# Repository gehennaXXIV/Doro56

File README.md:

# Doro56
***

A 56-key split keyboard with a reversible PCB that uses normal mods, an exploded number row, a semi-columnar staggered layout, plus support for rotary encoders. Mainly inspired by Alice layouts and split boards like the Lily58 and Corne.

[ZMK config](https://github.com/gehennaXXIV/zmk-config-Doro56)
 - support for https://nickcoutsos.github.io/keymap-editor/ and https://zmk.studio/

QMK config - None yet - RP2040 Pro Micro support soon

***
## Changelog

#### v1.2 - Minor Edit
- **JST PH Footprint**: The footprint has been updated to avoid the need for manually changing plug polarity. Ensure the Red (+) wire matches the plug's positive pin as the 2 outer pins are negative/ground pins. If your plug isn't matching the indicators, just shift the socket one pin sideways. Note: This socket is installed on the bottom of the half you're building.

#### v1.1 - Minor Edit
- **Caps and Enter Footprints**: Changed to a single reversible footprint (previously used two single key footprints rotated).
- **JST PH Footprint**: Adjusted and relocated for increased flexibility.
- **Plate**: Slightly increased the cutout size for the rotary encoder.
- **PCB Cutout**: Modified to [remove blank space](https://github.com/gehennaXXIV/Doro56/blob/main/pics/v1.1.png) between Control and Alt keys, allowing space for a 402030 battery without increasing the case height clearance.

***
## Build Guide
Quick overview:
* [Solder the MCU](https://raw.githubusercontent.com/gehennaXXIV/Doro56/main/pics/mcu.jpg) with the components facing down, and the TRRS jack on top of the half you are building. For MCU socketing, the footprint was modified to allow [sockets with thick pins to work](https://down-ph.img.susercontent.com/file/sg-11134201-7qvco-ley7fi4ef44v33). You can use milmax pins, or, what I use, harvested gold pins from a 5-pin RGB header (also cheaper). [Sample 2](https://raw.githubusercontent.com/gehennaXXIV/Doro56/main/pics/sockets.jpg)
* Bridge the [jumpers](https://raw.githubusercontent.com/gehennaXXIV/Doro56/main/pics/bridge.jpg) on the MCU from underneath, and add other components such as diodes, MX sockets, and the power switch.

***
## PARTS
| **COMPONENTS**             |  Qty  |  Remarks |
| :------------------------- | :---: | :------  |
| Diodes 1N4148W (SMD)        |  58   | SOD-123  |
| MX Switch Sockets           |  56   |          |
| 2U PCB-Mount Stabilizers    |  04   |          |
| Power Switch                |  02   | MSK12C02 |
| Reset Switch                |  02   | MJTP1250 |
| JST 2 PH Right Angle Jack   |  02   |          |
| TRRS Jack                   |  02   |  MJ-4PP-9 or PJ320A |
| Rotary Encoder              |  02   | EC11 - acrylic case has enough clearance for 22mm knobs |

***
| **MCU**                        |  Qty  |  Remarks |
| :----------------------------- | :---: | :------  |
| Low Profile MCU sockets        |  04   |  The MCU socket footprint was modified to allow [sockets with thick pins to work](https://down-ph.img.susercontent.com/file/sg-11134201-7qvco-ley7fi4ef44v33). This will make the build cheaper compared to buying Millmax sockets. |
| Mill Max Pins                  |  48   |  Mouser 3320-0-00-15-00-00-03-0, or a cheaper option: harvested gold pins from a 5-pin RGB header (just snip off the plastic parts) |
| Nice Nanos                     |  02   |  or NRF52840 clones |
| Li-Po Battery                  |  02   |  **Take note of the polarity before plugging the battery in.** [Here's a tutorial on how to change the polarity.](https://www.youtube.com/watch?v=za-azgbZor8) |

***
| **CASE**                                |  Qty  |  Remarks |
| :--------------------------------------- | :---: | :------  |
| [Acrylic Case](/Case/acrylic)            |  01   | Maybe a 3DP one soon, but I'm very content with the acrylic case. Let me know if you create one! |
| M2 6mm Wafer Head Screws                 |  20   | Plate screws |
| M2 10mm Round Standoff Spacer            |  10   | Plate standoffs, add +2mm if you need bottom clearance (see case readme) |
| M2 8mm Wafer Head Screws                 |  32   | Case screws |
| M2 13mm Round Standoff Spacer            |  16   | Case standoffs, add +2mm if you need bottom clearance (see case readme) ; can also be -1mm if it's protruding the middle layer |
| Rubber Feet                              |  08   | Currently, the keyboard lays flat. I’ve yet to design a base layer for angled feet |

***
## FOOTPRINTS USED
* https://github.com/ebastler/marbastlib
* https://github.com/joe-scotto/scottokeebs
* https://github.com/GEIGEIGEIST/KLOR
* https://github.com/50an6xy06r6n/keyboard_reversible.pretty

***
## DISCLAIMER
Please note that while this keyboard is provided as open-source, I am not liable for any issues, malfunctions, or other problems that may arise from its use. The keyboard is provided "as-is," and I make no warranties or guarantees regarding its performance or functionality. Use at your own risk.

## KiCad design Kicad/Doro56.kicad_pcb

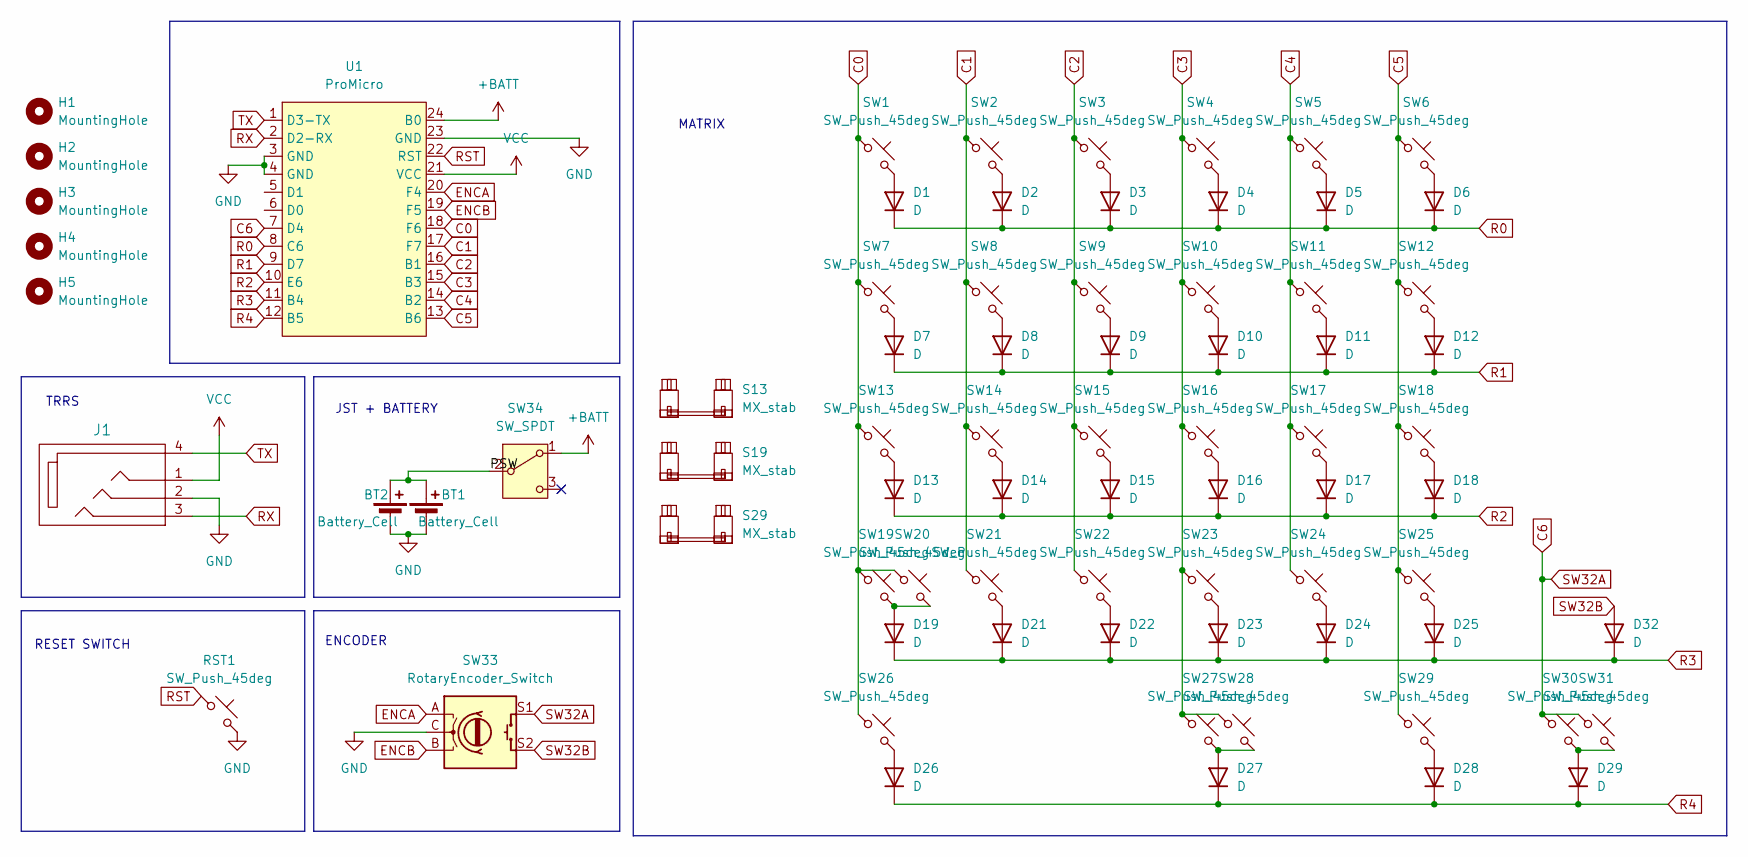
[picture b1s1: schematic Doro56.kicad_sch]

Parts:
BT1: Battery_Cell; JST_PH_2P_Reversible
BT2: Battery_Cell; custombatteryconnector_small
D1, D2, D3, D4, D5, D6, D7, D8, D9, D10, D11, D12, D13, D14, D15, D16, D17, D18, D19, D21, D22, D23, D24, D25, D26, D27, D28, D29, D32: D; Diode_SOD123
H1, H2, H3, H4, H5: MountingHole; MountingHole_3.2mm_M3
J1: MJ-4PP-9
RST1: SW_Push_45deg; Button_MJTP1243
S13, S19, S29: MX_stab; STAB_MX_2.25u
SW1, SW2, SW3, SW4, SW5, SW6, SW8, SW9, SW10, SW11, SW12, SW13, SW14, SW15, SW16, SW17, SW18, SW21, SW22, SW23, SW24, SW25: SW_Push_45deg; MX Rev 1U
SW7, SW26: SW_Push_45deg; MX Rev 1.5U
SW19: SW_Push_45deg; MX 2.25U
SW20: SW_Push_45deg; MX 1.75U
SW27, SW30: SW_Push_45deg; MX 1.25U
SW28, SW31: SW_Push_45deg; MX 1U
SW29: SW_Push_45deg; MX Rev 2.25U
SW33: RotaryEncoder_Switch; RotaryEncoder_Alps_EC11E-Switch_Vertical_H20mm-keebio_modif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
SW34: SW_SPDT; MSK12C02_reversible
U1: ProMicro; ProMicro_facedown_bigger_holes

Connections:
+BATT: SW34.1 (A), U1.24 (B0)
/PSW: BT1.1 (+), BT2.1 (+), SW34.2 (B)
C0: SW1.1, SW7.1, SW13.1, SW19.1, SW20.1, SW26.1, U1.18 (F6)
C1: SW2.1, SW8.1, SW14.1, SW21.1, U1.17 (F7)
C2: SW3.1, SW9.1, SW15.1, SW22.1, U1.16 (B1)
C3: SW4.1, SW10.1, SW16.1, SW23.1, SW27.1, SW28.1, U1.15 (B3)
C4: SW5.1, SW11.1, SW17.1, SW24.1, U1.14 (B2)
C5: SW6.1, SW12.1, SW18.1, SW25.1, SW29.1, U1.13 (B6)
C6: SW30.1, SW31.1, SW33.S1, U1.7 (D4)
ENCA: SW33.A, U1.20 (F4)
ENCB: SW33.B, U1.19 (F5)
GND: BT1.2 (-), BT2.2 (-), J1.2, RST1.2, SW33.C, U1.3 (GND), U1.4 (GND), U1.23 (GND)
unnamed: D1.2 (A), SW1.2
unnamed: D2.2 (A), SW2.2
unnamed: D3.2 (A), SW3.2
unnamed: D4.2 (A), SW4.2
unnamed: D5.2 (A), SW5.2
unnamed: D6.2 (A), SW6.2
unnamed: D7.2 (A), SW7.2
unnamed: D8.2 (A), SW8.2
unnamed: D9.2 (A), SW9.2
unnamed: D10.2 (A), SW10.2
unnamed: D11.2 (A), SW11.2
unnamed: D12.2 (A), SW12.2
unnamed: D13.2 (A), SW13.2
unnamed: D14.2 (A), SW14.2
unnamed: D15.2 (A), SW15.2
unnamed: D16.2 (A), SW16.2
unnamed: D17.2 (A), SW17.2
unnamed: D18.2 (A), SW18.2
unnamed: D19.2 (A), SW19.2, SW20.2
unnamed: D21.2 (A), SW21.2
unnamed: D22.2 (A), SW22.2
unnamed: D23.2 (A), SW23.2
unnamed: D24.2 (A), SW24.2
unnamed: D25.2 (A), SW25.2
unnamed: D26.2 (A), SW26.2
unnamed: D27.2 (A), SW27.2, SW28.2
unnamed: D28.2 (A), SW29.2
unnamed: D29.2 (A), SW30.2, SW31.2
R0: D1.1 (K), D2.1 (K), D3.1 (K), D4.1 (K), D5.1 (K), D6.1 (K), U1.8 (C6)
R1: D7.1 (K), D8.1 (K), D9.1 (K), D10.1 (K), D11.1 (K), D12.1 (K), U1.9 (D7)
R2: D13.1 (K), D14.1 (K), D15.1 (K), D16.1 (K), D17.1 (K), D18.1 (K), U1.10 (E6)
R3: D19.1 (K), D21.1 (K), D22.1 (K), D23.1 (K), D24.1 (K), D25.1 (K), D32.1 (K), U1.11 (B4)
R4: D26.1 (K), D27.1 (K), D28.1 (K), D29.1 (K), U1.12 (B5)
RST: RST1.1, U1.22 (RST)
RX: J1.3, U1.2 (D2-RX)
SW32B: D32.2 (A), SW33.S2
TX: J1.4, U1.1 (D3-TX)
VCC: J1.1, U1.21 (VCC)

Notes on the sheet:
TRRS
RESET SWITCH
JST + BATTERY
MATRIX
ENCODER

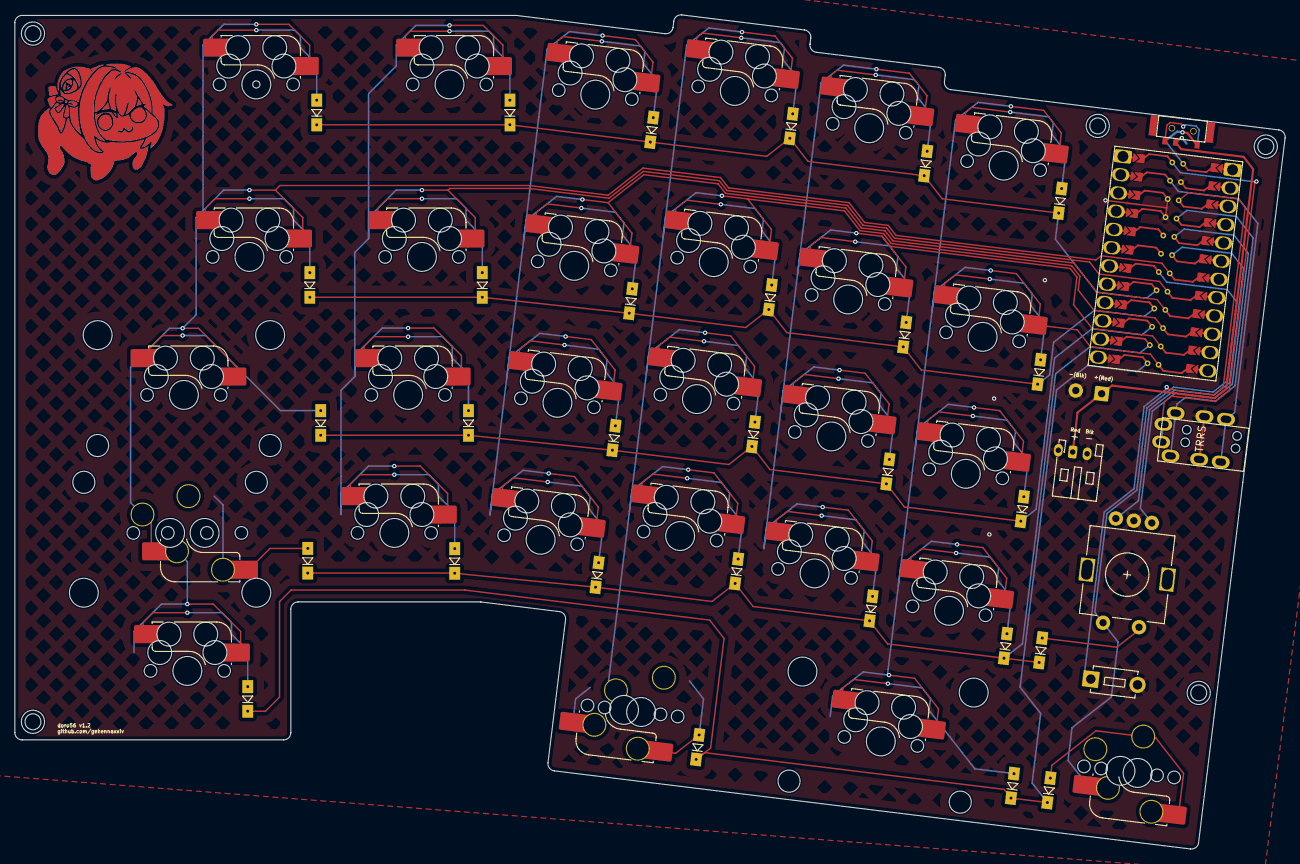
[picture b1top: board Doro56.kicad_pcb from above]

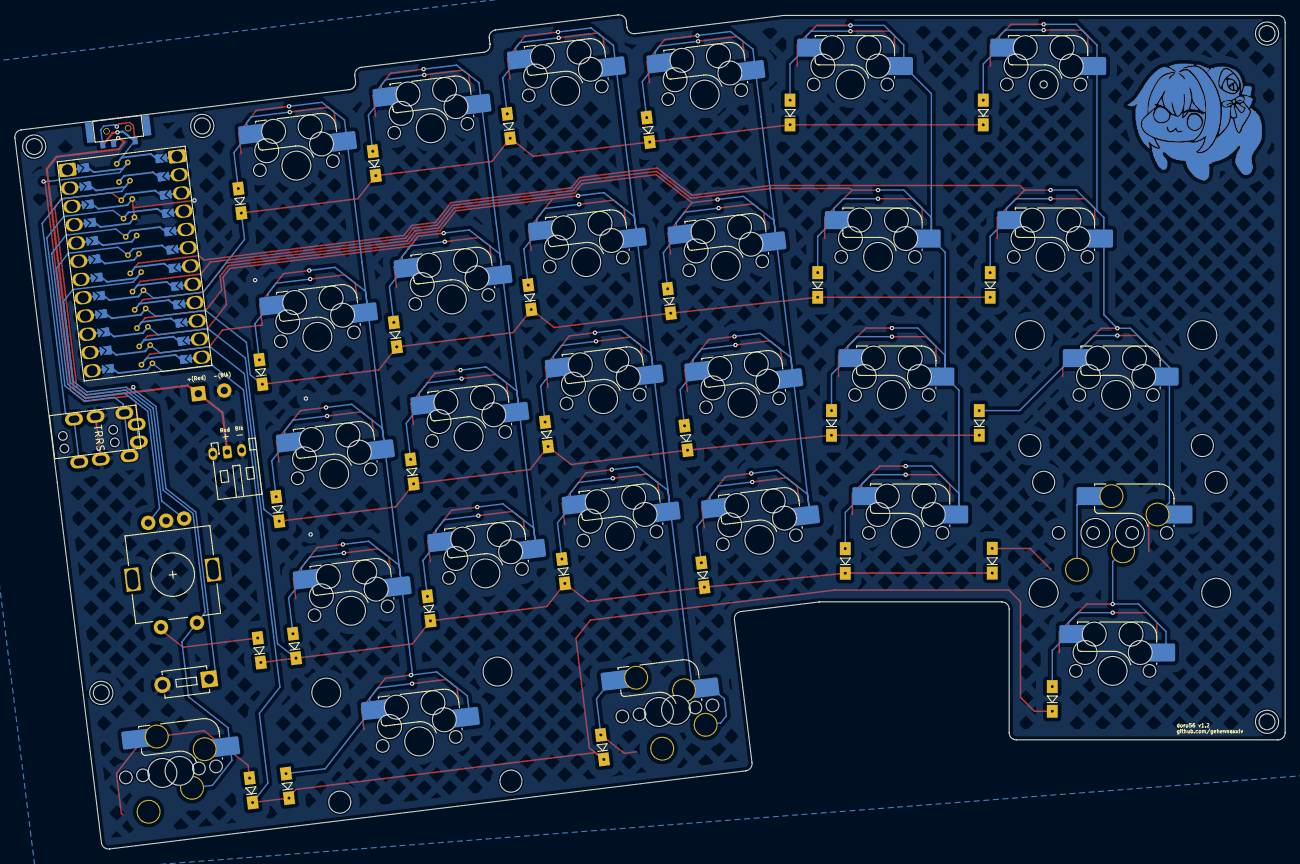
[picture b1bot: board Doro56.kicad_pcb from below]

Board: 2 copper layers, 175.4 x 115.2 mm, 75 parts (6 on the bottom side), 50 nets.

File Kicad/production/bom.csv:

Designator,Footprint,Quantity,Value,LCSC Part #
BT1,JST_PH_2P_Reversible,1,Battery_Cell,
BT2,custombatteryconnector_small,1,Battery_Cell,
"D1, D10, D11, D12, D13, D14, D15, D16, D17, D18, D19, D2, D21, D22, D23, D24, D25, D26, D27, D28, D29, D3, D32, D4, D5, D6, D7, D8, D9",Diode_SOD123,29,D,
J1,MJ-4PP-9,1,MJ-4PP-9,
RST1,Button_MJTP1243,1,SW_Push_45deg,
"S13, S19, S29",STAB_MX_2.25u,3,MX_stab,
"SW1, SW10, SW11, SW12, SW13, SW14, SW15, SW16, SW17, SW18, SW2, SW21, SW22, SW23, SW24, SW25, SW3, SW4, SW5, SW6, SW8, SW9",MX Rev 1U,22,SW_Push_45deg,
SW19,MX 2.25U,1,SW_Push_45deg,
SW20,MX 1.75U,1,SW_Push_45deg,
"SW26, SW7",MX Rev 1.5U,2,SW_Push_45deg,
"SW27, SW30",MX 1.25U,2,SW_Push_45deg,
"SW28, SW31",MX 1U,2,SW_Push_45deg,
SW29,MX Rev 2.25U,1,SW_Push_45deg,
SW33,RotaryEncoder_Alps_EC11E-Switch_Vertical_H20mm-keebio_modified,1,RotaryEncoder_Switch,
SW34,MSK12C02_reversible,1,SW_SPDT,

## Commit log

2024-08-15 blocker fix
2024-08-17 Create LICENSE
2024-08-18 pcb pic
2024-08-20 resize
2024-08-20 edit
2024-08-27 v1.1
    v1.1 - Minor Edit
    Caps and Enter Footprints: Changed to a reversible footprint (previously used two single key footprints rotated).
    JST PH Footprint: Adjusted and relocated for increased flexibility.
    PCB Cutout: Modified to remove blank space between Control and Alt keys, allowing space for a 402030 battery without increasing the case height clearance.
    Plate: Slightly increased the cutout size for the rotary encoder.
2024-08-31 yeet lego case
2024-08-31 docs update
2024-10-23 cleanup
2024-11-12 docs
